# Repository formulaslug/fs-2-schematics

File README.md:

# This is outdated (June 2024)

<p align="center">
  
  <h3 align="center">FS-2 Schematics</h3>

  <p align="center">
    This is the electrical schematics repository for the FS-2 racecar.
    <br />
    <a href="https://github.com/formulaslug/fs-2-schematics/issues">Report Bug</a>
    ·
    <a href="https://github.com/formulaslug/fs-2-schematics/issues">Request Feature</a>
  </p>
</p>

## Getting started
In depth version of how to get started 🏎️
#### Tools that we are using
* [GitHub](https://github.com)
* [KiCAD](https://kicad-pcb.org/)

1) First, download [KiCAD for your specific OS](https://kicad-pcb.org/download/)

2) Next, make sure you have Git installed.

* [GitHub Desktop](https://desktop.github.com/)
If you are *not* tech savvy
* [Git](https://git-scm.com/downloads)
If you are tech savvy 😎

If you installed GitHub desktop, create an account and close the repository.
I recommend cloning the repository into your documents folder.

[How to clone repositories on GitHub desktop](https://docs.github.com/en/free-pro-team@latest/desktop/contributing-and-collaborating-using-github-desktop/cloning-and-forking-repositories-from-github-desktop)

The repository url is: https://github.com/formulaslug/fs-2-schematics

If you are <b>tech savvy</b> and using Git

`$ git clone https://github.com/formulaslug/fs-2-schematics`

3) Setting the project file path correctly on KiCAD

Make sure KiCAD is currently open

Then click on `preferences -> Configure Paths..`

Click on the plus on the bottom right to add a new path variable

On the left, you want it `FS_2_SCHEMATICS` <- all caps

On the right, you want to set the path where you installed the repository (the folder is called `fs-2-schematics`)

Click on the folder on the right, and find `fs-2-schematics` repo like stated above

Should look something like this after its done

Example (might look different if you are using an Mac, or Linux):

Left side | Right side
------------ | -------------
FS_2_SCHEMATICS | Docs\fs-2-schematics

4) Lastly, open up the project

## Contributing guide

## Projects

### BMS

This is the design for the LTC6811-based BMS module, based on the design from fs-1.

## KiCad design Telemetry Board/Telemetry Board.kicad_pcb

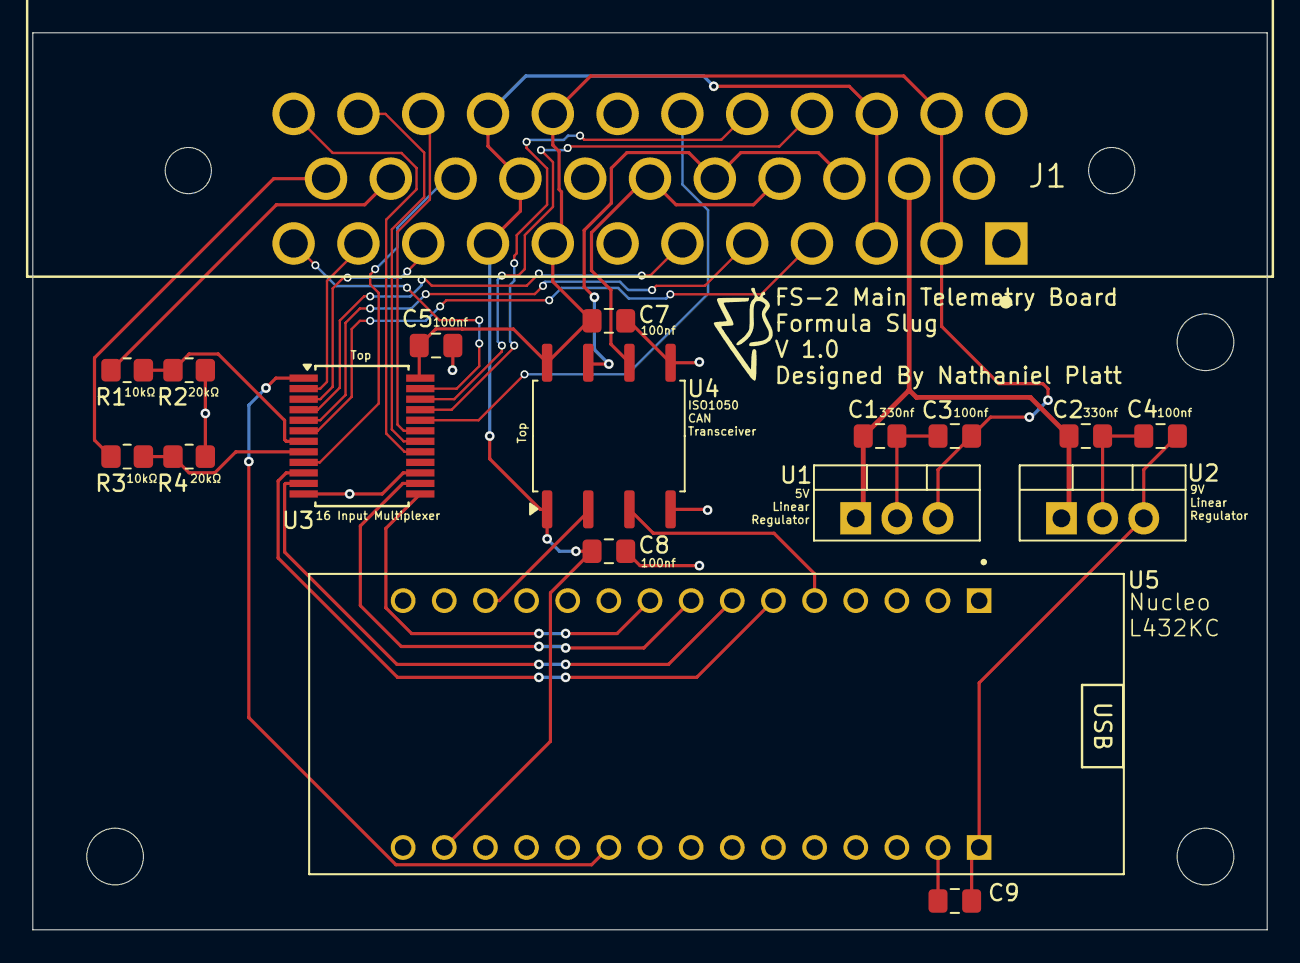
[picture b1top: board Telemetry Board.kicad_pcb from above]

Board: 2 copper layers, 76.2 x 55.4 mm, 18 parts (0 on the bottom side), 31 nets.

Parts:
C1, C2: 330nf; C_0805_2012Metric_Pad1.18x1.45mm_HandSolder
C3, C4, C5, C7, C8, C9: 100nf; C_0805_2012Metric_Pad1.18x1.45mm_HandSolder
J1: 776180-1; TE_776180-1
R1, R3: 10k; R_0805_2012Metric_Pad1.20x1.40mm_HandSolder
R2, R4: 20k; R_0805_2012Metric_Pad1.20x1.40mm_HandSolder
U1: LM7805_TO220; TO-220-3_Vertical
U2: LM7809_TO220; TO-220-3_Vertical
U3: CD74HC4067SM96; SSOP-24_5.3x8.2mm_P0.65mm
U4: ISO1050DUB; SOP-8_6.62x9.15mm_P2.54mm
U5: NUCLEO-L432KC; MODULE_NUCLEO-L432KC

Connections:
+3V3: C8.2, J1.3, J1.9, J1.20, J1.26, J1.32, U4.1 (VCC1), U5.CN4_14 (3V3)
+5V: C3.1, C5.1, C7.2, J1.2, J1.8, J1.25, J1.31, U1.3 (VO), U3.24 (VCC), U4.8 (VCC2)
+9V: C4.1, C9.1, U2.3 (VO), U5.CN4_1 (VIN)
+12V: C1.1, C2.1, J1.14, U1.1 (VI), U2.1 (VI)
/CAN1_RD: U4.2 (RXD), U5.CN3_13 (PA11)
/CAN1_TD: U4.3 (TXD), U5.CN3_5 (PA12)
ADC: U3.1 (COMMON_I_O), U5.CN4_10 (PA3)
Brake Sensor B: J1.23, R3.1
Brake Sensor F: J1.22, R1.1
Brake Sensor F 3V3: R1.2, R2.2, U3.7 (I2)
Brake Sensor R 3V3: R3.2, R4.2, U3.8 (I1)
CAN_H: J1.15, J1.17, U4.7 (CANH)
CAN_L: J1.16, J1.18, U4.6 (CANL)
GND: C1.2, C2.2, C3.2, C4.2, C5.2, C7.1, C8.1, C9.2, J1.1, J1.7, J1.13, J1.19, J1.24, J1.30, R2.1, R4.1, U1.2 (GND), U2.2 (GND), U3.12 (GND), U3.15 (E_N), U4.4 (GND1), U4.5 (GND2), U5.CN4_2 (GND)
S1: U3.10 (S0), U5.CN3_6 (PB0)
S2: U3.11 (S1), U5.CN3_7 (PB7)
S3: U3.14 (S2), U5.CN3_8 (PB6)
S4: U3.13 (S3), U5.CN3_9 (PB1)
Shock Position BL: J1.33, U3.19 (I12)
Shock Position BR: J1.27, U3.22 (I9)
Shock Position FL: J1.10, U3.3 (I6)
Shock Position FR: J1.4, U3.6 (I3)
Steering Sensor: J1.21, U3.9 (I0)
Strain BL: J1.34, U3.18 (I13)
Strain BR: J1.28, U3.21 (I10)
Strain FL: J1.11, U3.2 (I7)
Strain FR: J1.5, U3.5 (I4)
Wheel Speed BL: J1.35, U3.17 (I14)
Wheel Speed BR: J1.29, U3.20 (I11)
Wheel Speed FL: J1.12, U3.23 (I8)
Wheel Speed FR: J1.6, U3.4 (I5)

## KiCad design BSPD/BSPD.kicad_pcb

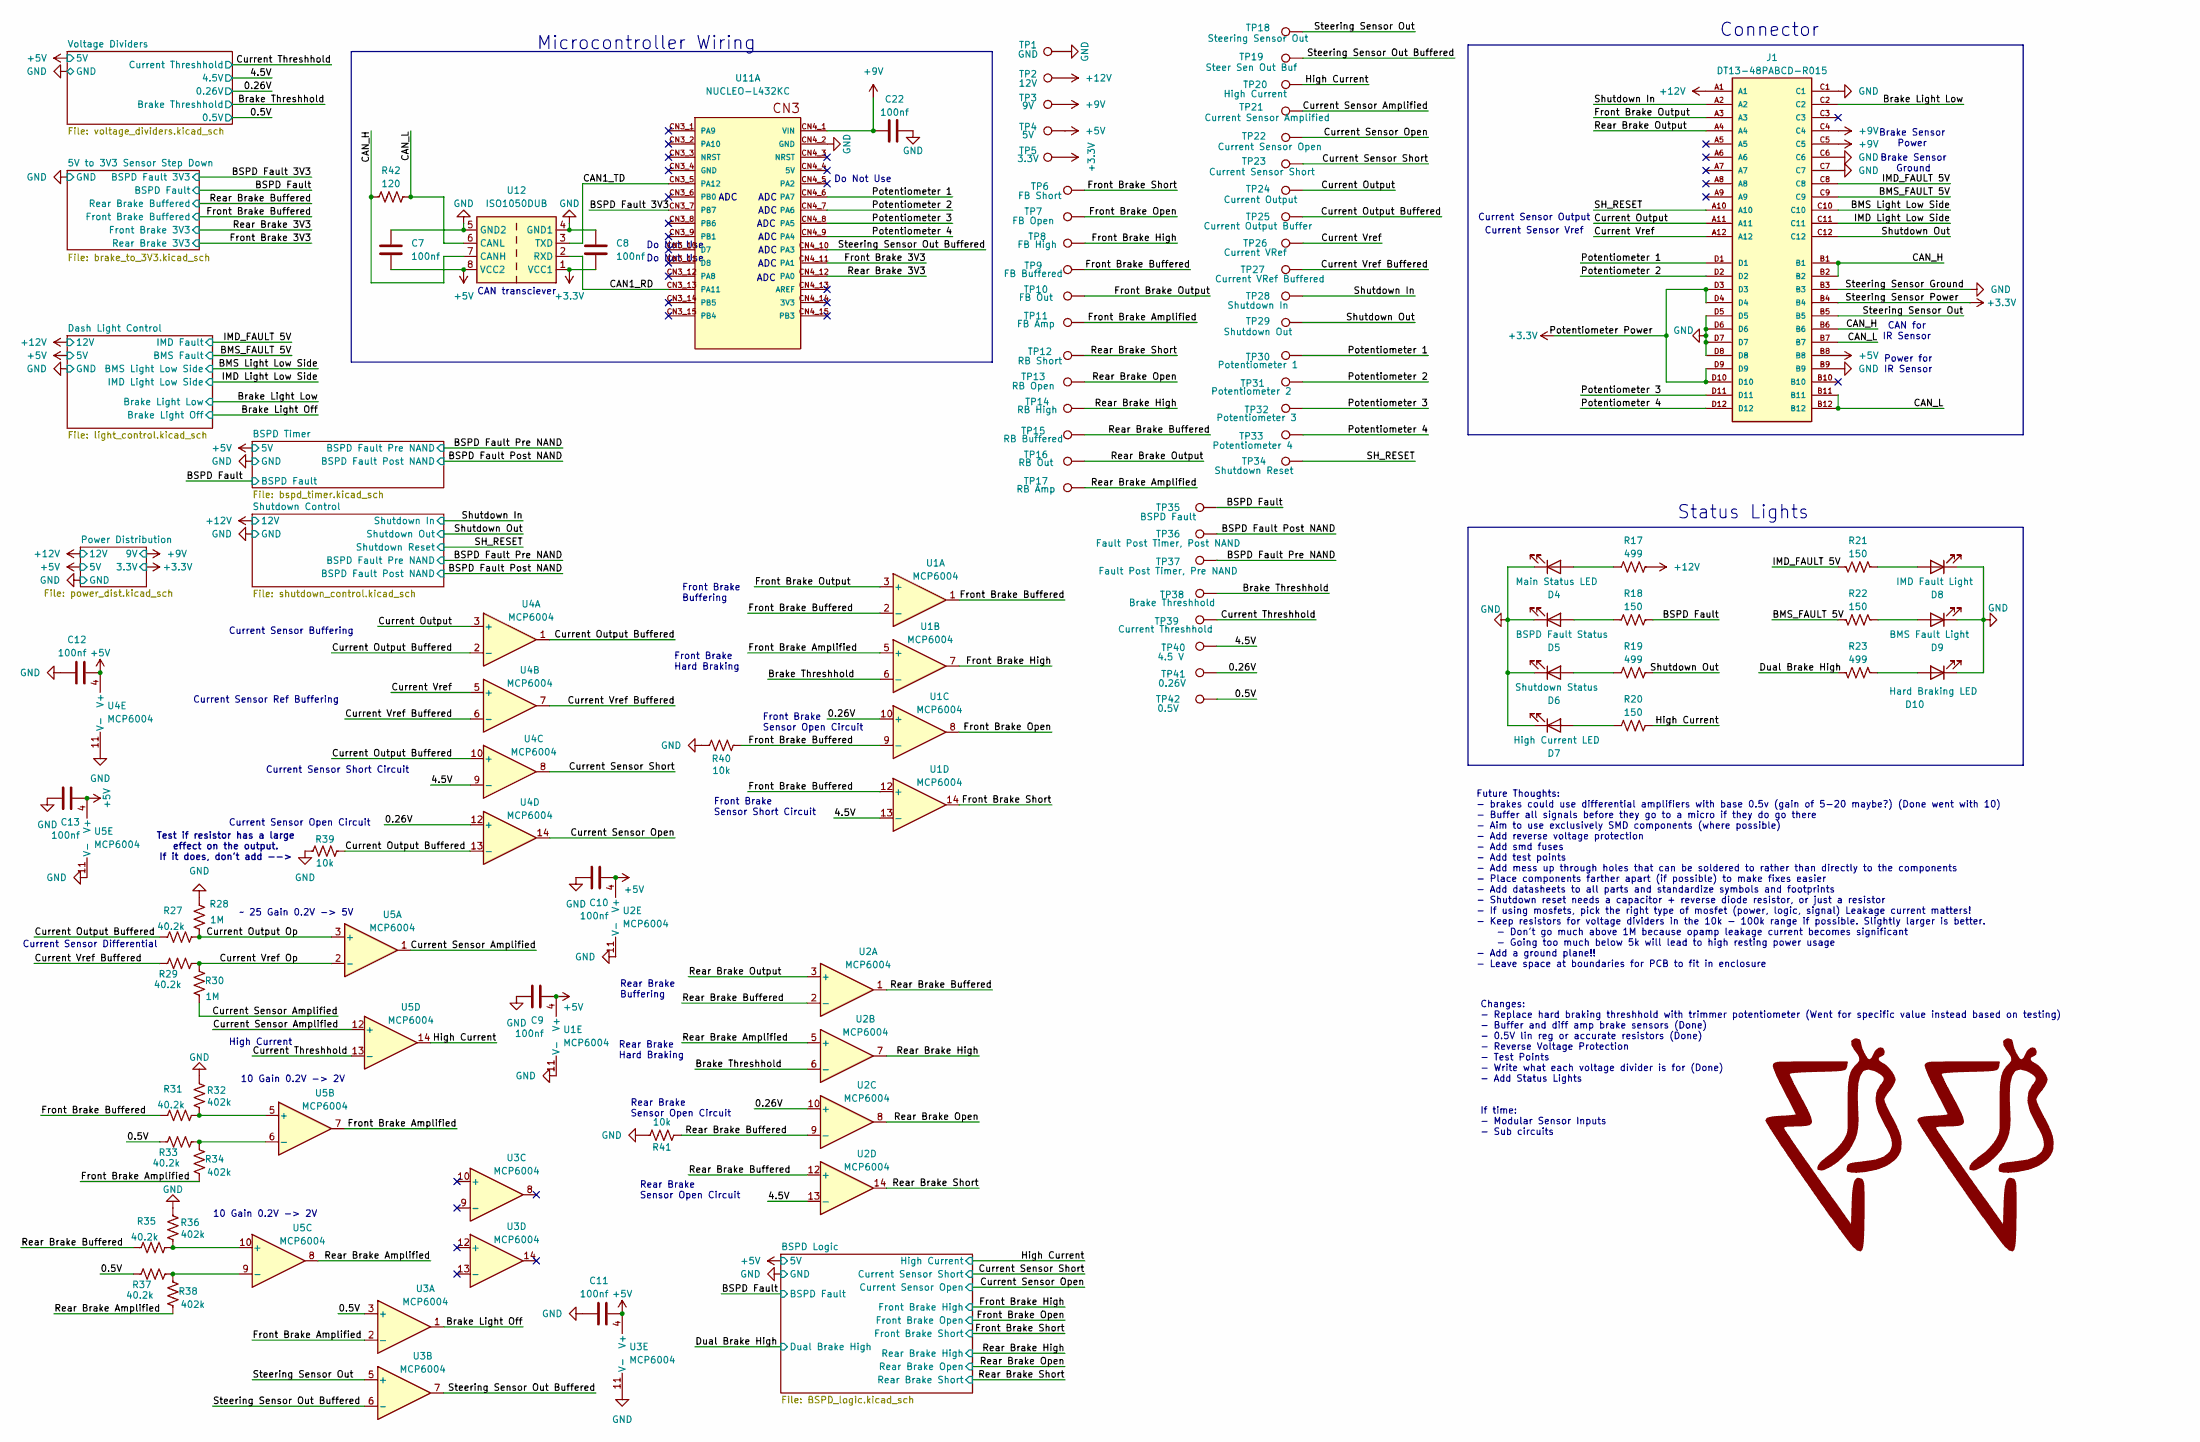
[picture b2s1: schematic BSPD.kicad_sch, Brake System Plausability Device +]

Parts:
C7, C8, C9, C10, C11, C12, C13, C22: 100nf; C_0805_2012Metric_Pad1.18x1.45mm_HandSolder
D4: Main Status LED; D_0805_2012Metric_Pad1.15x1.40mm_HandSolder
D5: BSPD Fault Status; D_0805_2012Metric_Pad1.15x1.40mm_HandSolder
D6: Shutdown Status; D_0805_2012Metric_Pad1.15x1.40mm_HandSolder
D7: High Current LED; D_0805_2012Metric_Pad1.15x1.40mm_HandSolder
D8: IMD Fault Light; D_0805_2012Metric_Pad1.15x1.40mm_HandSolder
D9: BMS Fault Light; D_0805_2012Metric_Pad1.15x1.40mm_HandSolder
D10: Hard Braking LED; D_0805_2012Metric_Pad1.15x1.40mm_HandSolder
G1: FS Logo; FS Logo Big
G2: FS Logo; FORMULA SLUG
J1: DT13-48PABCD-R015; TE_DT13-48PABCD-R015; PARTREV NC
R17, R19, R23: 499; R_0805_2012Metric_Pad1.20x1.40mm_HandSolder
R18, R20, R21, R22: 150; R_0805_2012Metric_Pad1.20x1.40mm_HandSolder
R27, R29, R31, R33, R35, R37: 40.2k; R_0805_2012Metric_Pad1.20x1.40mm_HandSolder
R28, R30: 1M; R_0805_2012Metric_Pad1.20x1.40mm_HandSolder
R32, R34, R36, R38: 402k; R_0805_2012Metric_Pad1.20x1.40mm_HandSolder
R39, R40, R41: 10k; R_0805_2012Metric_Pad1.20x1.40mm_HandSolder
R42: 120; R_0805_2012Metric_Pad1.20x1.40mm_HandSolder
TP1: GND; TestPoint_Loop_D2.50mm_Drill1.0mm
TP2: 12V; TestPoint_Loop_D2.50mm_Drill1.0mm
TP3: 9V; TestPoint_Loop_D2.50mm_Drill1.0mm
TP4: 5V; TestPoint_Loop_D2.50mm_Drill1.0mm
TP5: 3.3V; TestPoint_Loop_D2.50mm_Drill1.0mm
TP6: FB Short; TestPoint_Loop_D2.50mm_Drill1.0mm
TP7: FB Open; TestPoint_Loop_D2.50mm_Drill1.0mm
TP8: FB High; TestPoint_Loop_D2.50mm_Drill1.0mm
TP9: FB Buffered; TestPoint_Loop_D2.50mm_Drill1.0mm
TP10: FB Out; TestPoint_Loop_D2.50mm_Drill1.0mm
TP11: FB Amp; TestPoint_Loop_D2.50mm_Drill1.0mm
TP12: RB Short; TestPoint_Loop_D2.50mm_Drill1.0mm
TP13: RB Open; TestPoint_Loop_D2.50mm_Drill1.0mm
TP14: RB High; TestPoint_Loop_D2.50mm_Drill1.0mm
TP15: RB Buffered; TestPoint_Loop_D2.50mm_Drill1.0mm
TP16: RB Out; TestPoint_Loop_D2.50mm_Drill1.0mm
TP17: RB Amp; TestPoint_Loop_D2.50mm_Drill1.0mm
TP18: Steering Sensor Out; TestPoint_Loop_D2.50mm_Drill1.0mm
TP19: Steer Sen Out Buf; TestPoint_Loop_D2.50mm_Drill1.0mm
TP20: High Current; TestPoint_Loop_D2.50mm_Drill1.0mm
TP21: Current Sensor Amplified; TestPoint_Loop_D2.50mm_Drill1.0mm
TP22: Current Sensor Open; TestPoint_Loop_D2.50mm_Drill1.0mm
TP23: Current Sensor Short; TestPoint_Loop_D2.50mm_Drill1.0mm
TP24: Current Output; TestPoint_Loop_D2.50mm_Drill1.0mm
TP25: Current Output Buffer; TestPoint_Loop_D2.50mm_Drill1.0mm
TP26: Current VRef; TestPoint_Loop_D2.50mm_Drill1.0mm
TP27: Current VRef Buffered; TestPoint_Loop_D2.50mm_Drill1.0mm
TP28: Shutdown In; TestPoint_Loop_D2.50mm_Drill1.0mm
TP29: Shutdown Out; TestPoint_Loop_D2.50mm_Drill1.0mm
TP30: Potentiometer 1; TestPoint_Loop_D2.50mm_Drill1.0mm
TP31: Potentiometer 2; TestPoint_Loop_D2.50mm_Drill1.0mm
TP32: Potentiometer 3; TestPoint_Loop_D2.50mm_Drill1.0mm
TP33: Potentiometer 4; TestPoint_Loop_D2.50mm_Drill1.0mm
TP34: Shutdown Reset; TestPoint_Loop_D2.50mm_Drill1.0mm
TP35: BSPD Fault; TestPoint_Loop_D2.50mm_Drill1.0mm
TP36: Fault Post Timer, Post NAND; TestPoint_Loop_D2.50mm_Drill1.0mm
TP37: Fault Post Timer, Pre NAND; TestPoint_Loop_D2.50mm_Drill1.0mm
TP38: Brake Threshhold; TestPoint_Loop_D2.50mm_Drill1.0mm
TP39: Current Threshhold; TestPoint_Loop_D2.50mm_Drill1.0mm
TP40: 4.5 V; TestPoint_Loop_D2.50mm_Drill1.0mm
TP41: 0.26V; TestPoint_Loop_D2.50mm_Drill1.0mm
TP42: 0.5V; TestPoint_Loop_D2.50mm_Drill1.0mm
U1, U2, U3, U4, U5: MCP6004; SOIC-14_3.9x8.7mm_P1.27mm
U11: NUCLEO-L432KC; MODULE_NUCLEO-L432KC; PARTREV N/A
U12: ISO1050DUB; SOP-8_6.62x9.15mm_P2.54mm

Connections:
+3.3V: C8.2, J1.B4, J1.D3, J1.D4, J1.D9, J1.D10, TP5.1, U12.1 (VCC1); also elsewhere on the board
+5V: C7.2, C9.2, C10.2, C11.2, C12.2, C13.2, J1.B8, TP4.1, U1.4 (V+), U2.4 (V+), U3.4 (V+), U4.4 (V+), U5.4 (V+), U12.8 (VCC2); also elsewhere on the board
+9V: C22.1, J1.C4, J1.C5, TP3.1, U11.CN4_1 (VIN); also elsewhere on the board
+12V: J1.A1, R17.1, TP2.1; also elsewhere on the board
/0.5V: R33.1, R37.1, TP42.1, U3.3 (+); also elsewhere on the board
/0.26V: TP41.1, U1.10 (+), U2.10 (+), U4.12 (+); also elsewhere on the board
/4.5V: TP40.1, U1.13 (-), U2.13 (-), U4.9 (-); also elsewhere on the board
/BMS Light Low Side: J1.C10; also elsewhere on the board
/BMS_FAULT 5V: J1.C9, R22.1; also elsewhere on the board
/BSPD Fault: R18.1, TP35.1; also elsewhere on the board
/BSPD Fault 3V3: U11.CN3_7 (PB7); also elsewhere on the board
/BSPD Fault Post NAND: TP36.1; also elsewhere on the board
/BSPD Fault Pre NAND: TP37.1; also elsewhere on the board
/Brake Light Low: J1.C2; also elsewhere on the board
/Brake Light Off: U3.1; also elsewhere on the board
/Brake Threshhold: TP38.1, U1.6 (-), U2.6 (-); also elsewhere on the board
/CAN1_RD: U11.CN3_13 (PA11), U12.2 (RXD)
/CAN1_TD: U11.CN3_5 (PA12), U12.3 (TXD)
/CAN_H: J1.B1, J1.B2, J1.B6, R42.2, U12.7 (CANH)
/CAN_L: J1.B7, J1.B11, J1.B12, R42.1, U12.6 (CANL)
/Current Output: J1.A11, TP24.1, U4.3 (+)
/Current Output Buffered: R27.2, R39.2, TP25.1, U4.1, U4.2 (-), U4.10 (+), U4.13 (-)
/Current Output Op: R27.1, R28.1, U5.3 (+)
/Current Sensor Amplified: R30.1, TP21.1, U5.1, U5.12 (+)
/Current Sensor Open: TP22.1, U4.14; also elsewhere on the board
/Current Sensor Short: TP23.1, U4.8; also elsewhere on the board
/Current Threshhold: TP39.1, U5.13 (-); also elsewhere on the board
/Current Vref: J1.A12, TP26.1, U4.5 (+)
/Current Vref Buffered: R29.1, TP27.1, U4.6 (-), U4.7
/Current Vref Op: R29.2, R30.2, U5.2 (-)
/Dual Brake High: R23.1; also elsewhere on the board
/Front Brake 3V3: U11.CN4_11 (PA1); also elsewhere on the board
/Front Brake Amplified: R34.1, TP11.1, U1.5 (+), U3.2 (-), U5.7
/Front Brake Buffered: R31.2, R40.1, TP9.1, U1.1, U1.2 (-), U1.9 (-), U1.12 (+); also elsewhere on the board
/Front Brake High: TP8.1, U1.7; also elsewhere on the board
/Front Brake Open: TP7.1, U1.8; also elsewhere on the board
/Front Brake Output: J1.A3, TP10.1, U1.3 (+)
/Front Brake Short: TP6.1, U1.14; also elsewhere on the board
/High Current: R20.1, TP20.1, U5.14; also elsewhere on the board
/IMD Light Low Side: J1.C11; also elsewhere on the board
/IMD_FAULT 5V: J1.C8, R21.1; also elsewhere on the board
/Potentiometer 1: J1.D1, TP30.1, U11.CN4_6 (PA7)
/Potentiometer 2: J1.D2, TP31.1, U11.CN4_7 (PA6)
/Potentiometer 3: J1.D11, TP32.1, U11.CN4_8 (PA5)
/Potentiometer 4: J1.D12, TP33.1, U11.CN4_9 (PA4)
/Rear Brake 3V3: U11.CN4_12 (PA0); also elsewhere on the board
/Rear Brake Amplified: R38.1, TP17.1, U2.5 (+), U5.8
/Rear Brake Buffered: R35.2, R41.2, TP15.1, U2.1, U2.2 (-), U2.9 (-), U2.12 (+); also elsewhere on the board
/Rear Brake High: TP14.1, U2.7; also elsewhere on the board
/Rear Brake Open: TP13.1, U2.8; also elsewhere on the board
/Rear Brake Output: J1.A4, TP16.1, U2.3 (+)
/Rear Brake Short: TP12.1, U2.14; also elsewhere on the board
/SH_RESET: J1.A10, TP34.1; also elsewhere on the board
/Shutdown In: J1.A2, TP28.1; also elsewhere on the board
/Shutdown Out: J1.C12, R19.1, TP29.1; also elsewhere on the board
/Steering Sensor Out: J1.B5, TP18.1, U3.5 (+)
/Steering Sensor Out Buffered: TP19.1, U3.6 (-), U3.7, U11.CN4_10 (PA3)
GND: C7.1, C8.1, C9.1, C10.1, C11.1, C12.1, C13.1, C22.2, D4.1 (K), D5.1 (K), D6.1 (K), D7.1 (K), D8.1 (K), D9.1 (K), D10.1 (K), J1.B3, J1.B9, J1.C1, J1.C6, J1.C7, J1.D5, J1.D6, J1.D7, J1.D8, R28.2, R32.2, R36.2, R39.1, R40.2, R41.1, TP1.1, U1.11 (V-), U2.11 (V-), U3.11 (V-), U4.11 (V-), U5.11 (V-), U11.CN4_2 (GND), U12.4 (GND1), U12.5 (GND2); also elsewhere on the board
unnamed: D4.2 (A), R17.2
unnamed: D5.2 (A), R18.2
unnamed: D6.2 (A), R19.2
unnamed: D7.2 (A), R20.2
unnamed: D8.2 (A), R21.2
unnamed: D9.2 (A), R22.2
unnamed: D10.2 (A), R23.2
unnamed: R31.1, R32.1, U5.5 (+)
unnamed: R33.2, R34.2, U5.6 (-)
unnamed: R35.1, R36.1, U5.10 (+)
unnamed: R37.2, R38.2, U5.9 (-)

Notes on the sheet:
Future Thoughts: - brakes could use differential amplifiers with base 0.5v (gain of 5-20 maybe?) (Done went with 10) - Buffer all signals before they go to a micro if they do go there - Aim to use exclusively SMD components (where possible) - Add reverse voltage protection - Add smd fuses - Add tes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
CAN for IR Sensor
ADC
Do Not Use
Rear Brake Buffering
Power for IR Sensor
Current Sensor Output
Microcontroller Wiring
Brake Sensor Power
High Current
Rear Brake Sensor Open Circuit
Current Sensor Buffering
10 Gain 0.2V -> 2V
Rear Brake Hard Braking
Front Brake Buffering
CAN transciever
Current Sensor Open Circuit
Front Brake Sensor Open Circuit
Current Sensor Vref
Changes: - Replace hard braking threshhold with trimmer potentiometer (Went for specific value instead based on testing) - Buffer and diff amp brake sensors (Done) - 0.5V lin reg or accurate resistors (Done) - Reverse Voltage Protection - Test Points - Write what each voltage divider is for (Done) 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
Current Sensor Differential
Connector
Test if resistor has a large effect on the output. If it does, don't add -->
Current Sensor Short Circuit
Status Lights
Front Brake Sensor Short Circuit
Current Sensor Ref Buffering
~ 25 Gain 0.2V -> 5V
Brake Sensor Ground
Front Brake Hard Braking

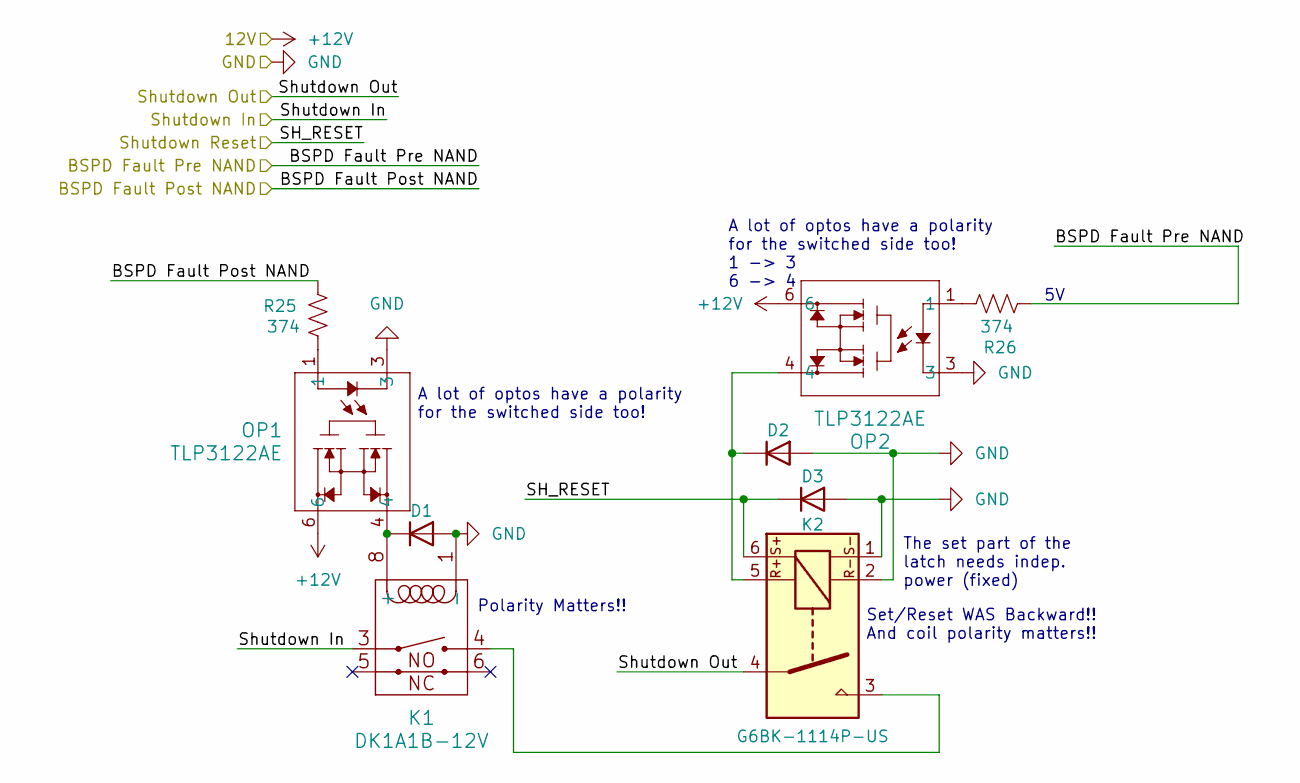
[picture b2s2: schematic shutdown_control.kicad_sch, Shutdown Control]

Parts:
D1, D2, D3: D; D_2010_5025Metric_Pad1.52x2.65mm_HandSolder
K1: DK1A1B-12V; RELAY_DK2A_PAN
K2: G6BK-1114P-US; Omron G6BK-1114P-US
OP1, OP2: TLP3122AE; OptoCoupler 6-SOP
R25, R26: 374; R_0805_2012Metric_Pad1.20x1.40mm_HandSolder

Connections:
+12V: OP1.6, OP2.6; also elsewhere on the board
/BSPD Fault Post NAND: R25.2; also elsewhere on the board
/BSPD Fault Pre NAND: R26.1; also elsewhere on the board
/SH_RESET: D3.1 (K), K2.6; also elsewhere on the board
/Shutdown In: K1.3; also elsewhere on the board
/Shutdown Out: K2.4; also elsewhere on the board
GND: D1.2 (A), D2.2 (A), D3.2 (A), K1.1 (-), K2.1, K2.2, OP1.3, OP2.3; also elsewhere on the board
unnamed: D1.1 (K), K1.8 (+), OP1.4
unnamed: D2.1 (K), K2.5, OP2.4
unnamed: K1.4, K2.3
unnamed: OP1.1, R25.1
unnamed: OP2.1, R26.2

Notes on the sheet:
A lot of optos have a polarity for the switched side too!
Set/Reset WAS Backward!! And coil polarity matters!!
A lot of optos have a polarity for the switched side too! 1 -> 3 6 -> 4
The set part of the latch needs indep. power (fixed)
Polarity Matters!!

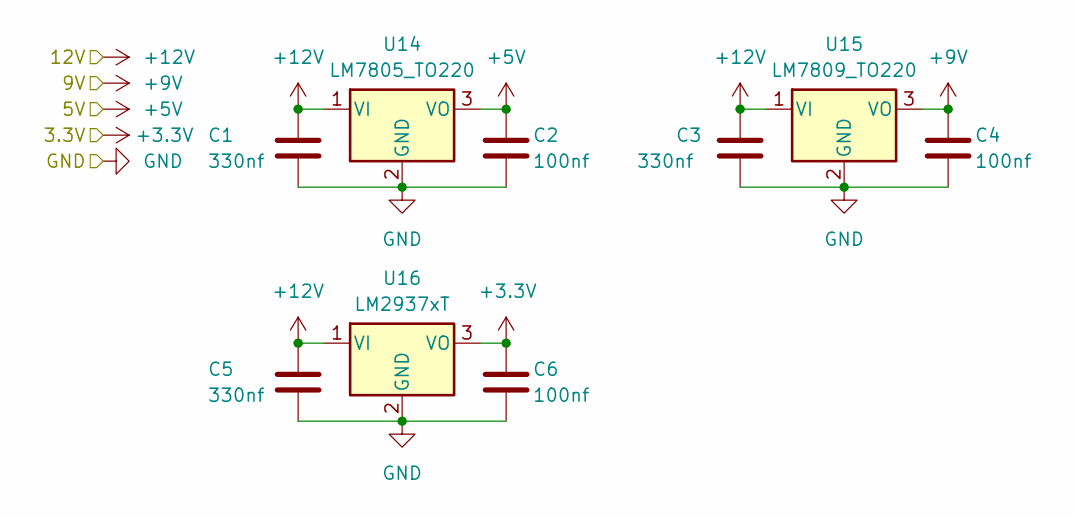
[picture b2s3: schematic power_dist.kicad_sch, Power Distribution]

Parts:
C1, C3, C5: 330nf; C_0805_2012Metric_Pad1.18x1.45mm_HandSolder
C2, C4, C6: 100nf; C_0805_2012Metric_Pad1.18x1.45mm_HandSolder
U14: LM7805_TO220; TO-220-3_Vertical
U15: LM7809_TO220; TO-220-3_Vertical
U16: LM2937xT; TO-220-3_Vertical

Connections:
+3.3V: C6.1, U16.3 (VO); also elsewhere on the board
+5V: C2.1, U14.3 (VO); also elsewhere on the board
+9V: C4.1, U15.3 (VO); also elsewhere on the board
+12V: C1.1, C3.1, C5.1, U14.1 (VI), U15.1 (VI), U16.1 (VI); also elsewhere on the board
GND: C1.2, C2.2, C3.2, C4.2, C5.2, C6.2, U14.2 (GND), U15.2 (GND), U16.2 (GND); also elsewhere on the board

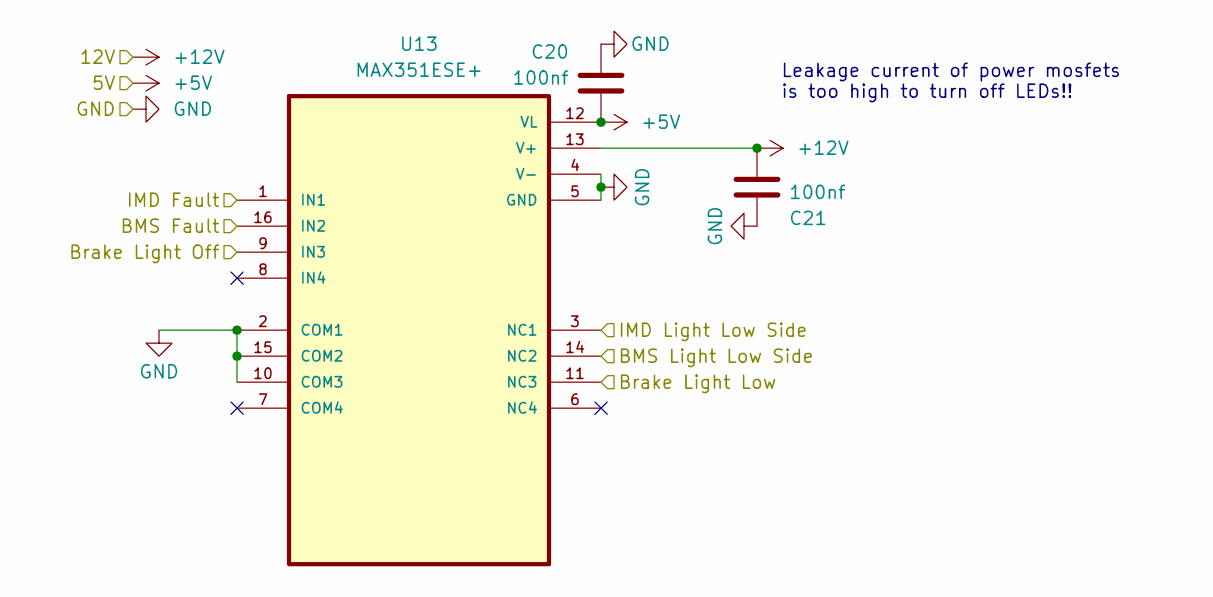
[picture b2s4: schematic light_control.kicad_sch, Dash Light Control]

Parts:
C20, C21: 100nf; C_0805_2012Metric_Pad1.18x1.45mm_HandSolder
U13: MAX351ESE+; SOIC127P600X175-16N

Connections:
+5V: C20.1, U13.12 (VL); also elsewhere on the board
+12V: C21.1, U13.13 (V+); also elsewhere on the board
/BMS Light Low Side: U13.14 (NC2); also elsewhere on the board
/BMS_FAULT 5V: U13.16 (IN2); also elsewhere on the board
/Brake Light Low: U13.11 (NC3); also elsewhere on the board
/Brake Light Off: U13.9 (IN3); also elsewhere on the board
/IMD Light Low Side: U13.3 (NC1); also elsewhere on the board
/IMD_FAULT 5V: U13.1 (IN1); also elsewhere on the board
GND: C20.2, C21.2, U13.2 (COM1), U13.4 (V-), U13.5 (GND), U13.10 (COM3), U13.15 (COM2); also elsewhere on the board

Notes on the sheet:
Leakage current of power mosfets is too high to turn off LEDs!!

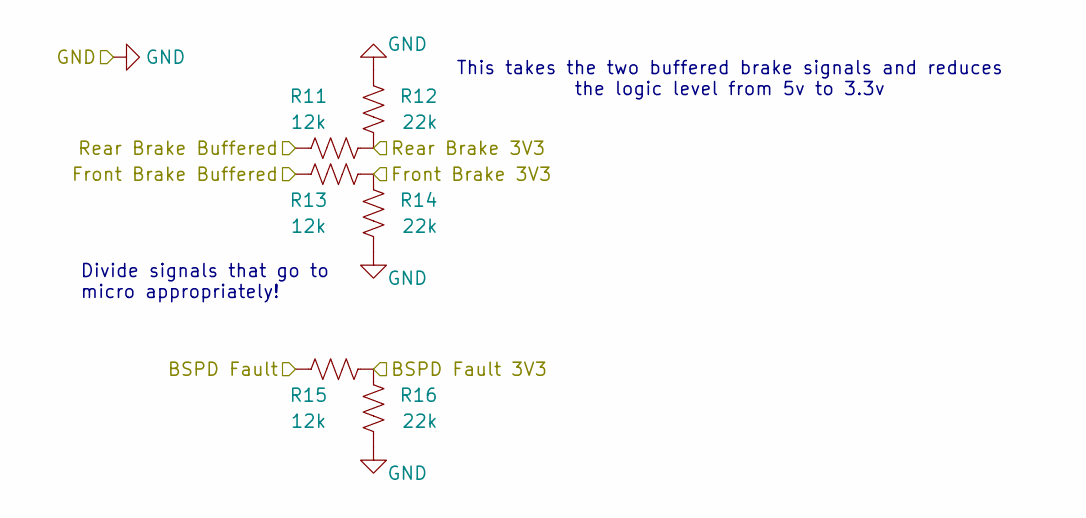
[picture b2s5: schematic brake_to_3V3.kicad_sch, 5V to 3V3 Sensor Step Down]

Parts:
R11, R13, R15: 12k; R_0805_2012Metric_Pad1.20x1.40mm_HandSolder
R12, R14, R16: 22k; R_0805_2012Metric_Pad1.20x1.40mm_HandSolder

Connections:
/BSPD Fault: R15.1; also elsewhere on the board
/BSPD Fault 3V3: R15.2, R16.2; also elsewhere on the board
/Front Brake 3V3: R11.2, R12.1; also elsewhere on the board
/Front Brake Buffered: R13.1; also elsewhere on the board
/Rear Brake 3V3: R13.2, R14.2; also elsewhere on the board
/Rear Brake Buffered: R11.1; also elsewhere on the board
GND: R12.2, R14.1, R16.1; also elsewhere on the board

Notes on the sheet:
Divide signals that go to micro appropriately!
This takes the two buffered brake signals and reduces the logic level from 5v to 3.3v

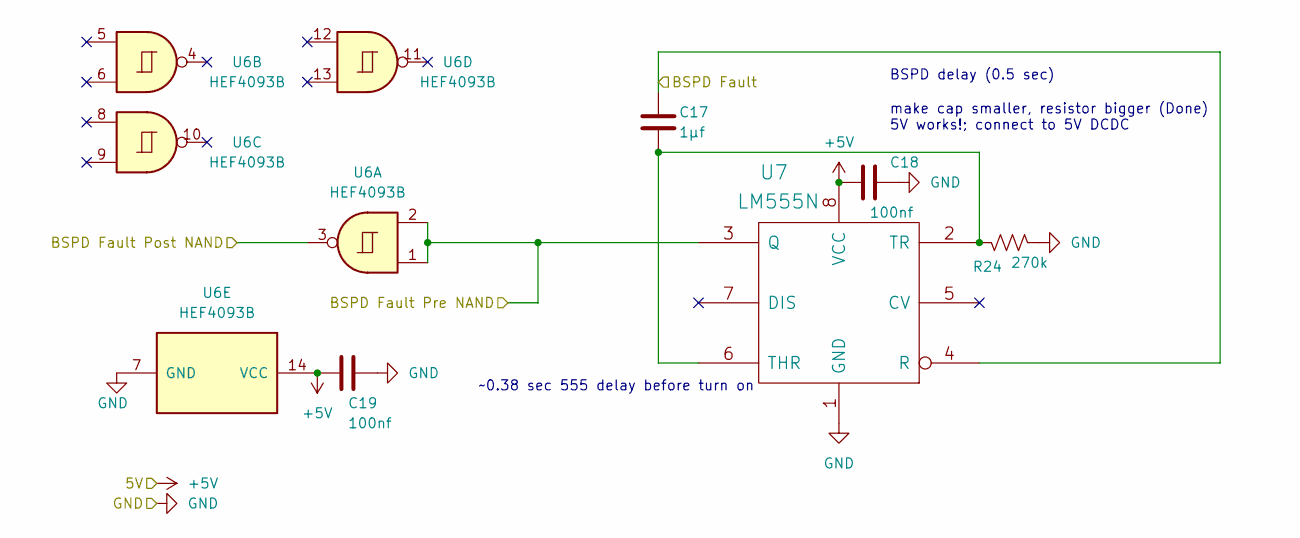
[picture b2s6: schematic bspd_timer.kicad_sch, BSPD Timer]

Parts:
C17: 1μf; C_0805_2012Metric_Pad1.18x1.45mm_HandSolder
C18, C19: 100nf; C_0805_2012Metric_Pad1.18x1.45mm_HandSolder
R24: 270k; R_0805_2012Metric_Pad1.20x1.40mm_HandSolder
U6: HEF4093B; SOIC-14_3.9x8.7mm_P1.27mm
U7: LM555N; DIP-8_W7.62mm

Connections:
+5V: C18.2, C19.2, U6.14 (VCC), U7.8 (VCC); also elsewhere on the board
/BSPD Fault: C17.1, U7.4 (R); also elsewhere on the board
/BSPD Fault Post NAND: U6.3; also elsewhere on the board
/BSPD Fault Pre NAND: U6.1, U6.2, U7.3 (Q); also elsewhere on the board
GND: C18.1, C19.1, R24.2, U6.7 (GND), U7.1 (GND); also elsewhere on the board
unnamed: C17.2, R24.1, U7.2 (TR), U7.6 (THR)

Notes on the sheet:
~0.38 sec 555 delay before turn on
BSPD delay (0.5 sec)
make cap smaller, resistor bigger (Done) 5V works!; connect to 5V DCDC

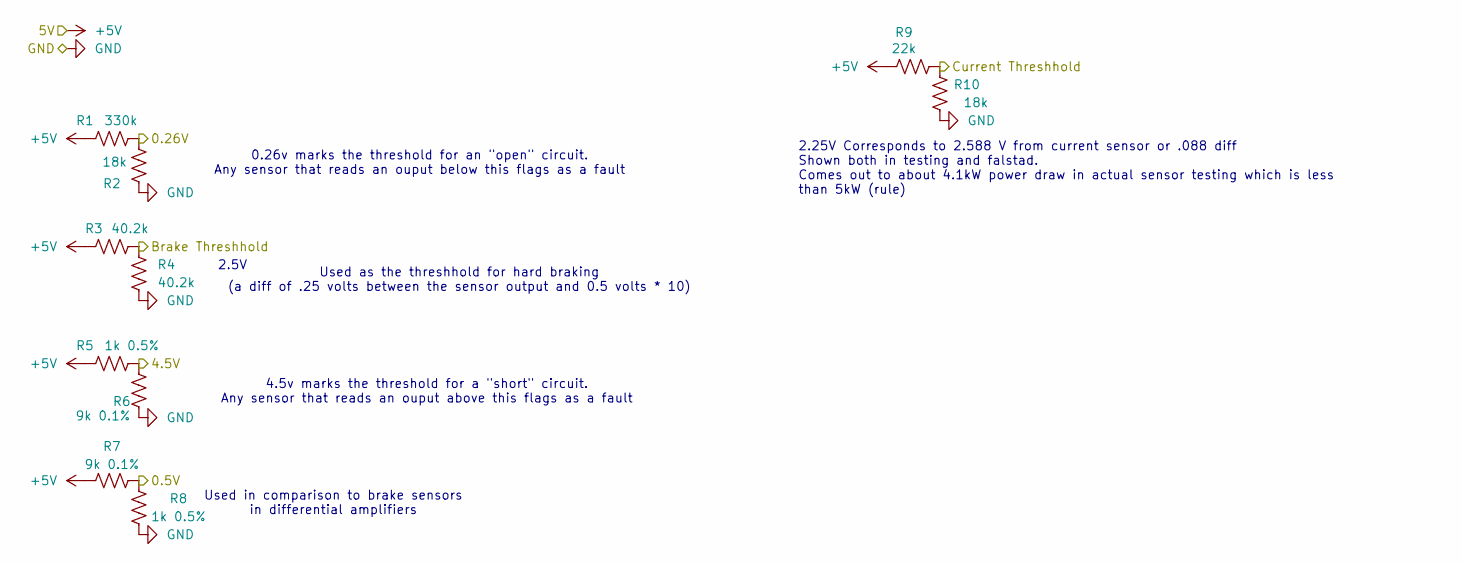
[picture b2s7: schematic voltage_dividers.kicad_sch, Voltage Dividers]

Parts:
R1: 330k; R_0805_2012Metric_Pad1.20x1.40mm_HandSolder
R2, R10: 18k; R_0805_2012Metric_Pad1.20x1.40mm_HandSolder
R3, R4: 40.2k; R_0805_2012Metric_Pad1.20x1.40mm_HandSolder
R5, R8: 1k 0.5%; R_0805_2012Metric_Pad1.20x1.40mm_HandSolder
R6, R7: 9k 0.1%; R_0805_2012Metric_Pad1.20x1.40mm_HandSolder
R9: 22k; R_0805_2012Metric_Pad1.20x1.40mm_HandSolder

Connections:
+5V: R1.1, R3.1, R5.1, R7.1, R9.2; also elsewhere on the board
/0.5V: R7.2, R8.2; also elsewhere on the board
/0.26V: R1.2, R2.1; also elsewhere on the board
/4.5V: R5.2, R6.1; also elsewhere on the board
/Brake Threshhold: R3.2, R4.1; also elsewhere on the board
/Current Threshhold: R9.1, R10.1; also elsewhere on the board
GND: R2.2, R4.2, R6.2, R8.1, R10.2; also elsewhere on the board

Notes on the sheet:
Used in comparison to brake sensors in differential amplifiers
2.25V Corresponds to 2.588 V from current sensor or .088 diff Shown both in testing and falstad. Comes out to about 4.1kW power draw in actual sensor testing which is less than 5kW (rule)
0.26v marks the threshold for an "open" circuit. Any sensor that reads an ouput below this flags as a fault
2.5V
Used as the threshhold for hard braking (a diff of .25 volts between the sensor output and 0.5 volts * 10)
4.5v marks the threshold for a "short" circuit. Any sensor that reads an ouput above this flags as a fault

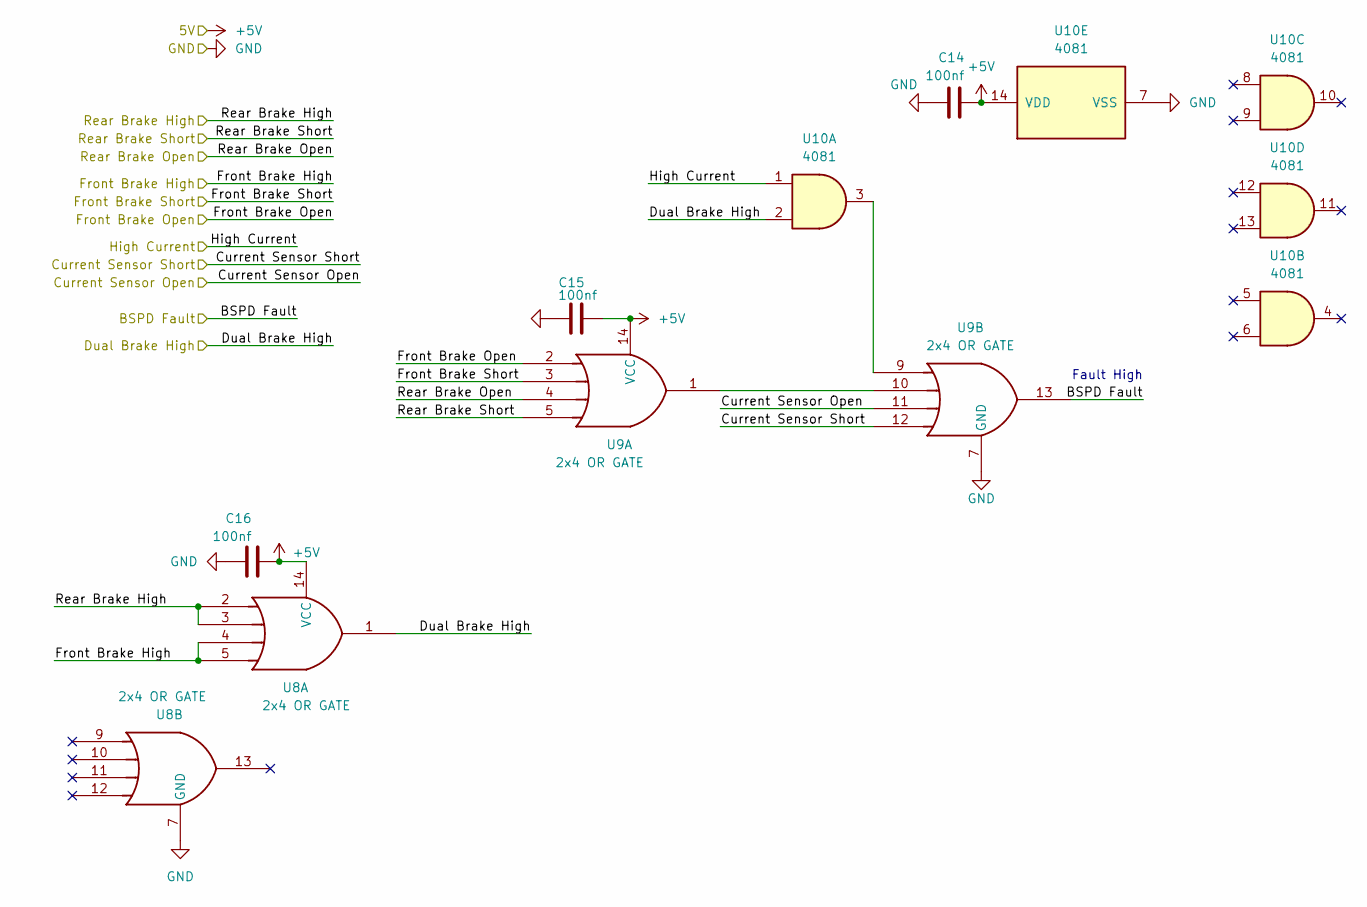
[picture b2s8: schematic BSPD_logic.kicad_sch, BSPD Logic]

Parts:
C14, C15, C16: 100nf; C_0805_2012Metric_Pad1.18x1.45mm_HandSolder
U8, U9: 2x4 OR GATE; DIP-14_W7.62mm
U10: 4081; SOIC-14_3.9x8.7mm_P1.27mm

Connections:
+5V: C14.2, C15.2, C16.2, U8.14 (VCC), U9.14 (VCC), U10.14 (VDD); also elsewhere on the board
/BSPD Fault: U9.13; also elsewhere on the board
/Current Sensor Open: U9.11; also elsewhere on the board
/Current Sensor Short: U9.12; also elsewhere on the board
/Dual Brake High: U8.1, U10.2; also elsewhere on the board
/Front Brake High: U8.4, U8.5; also elsewhere on the board
/Front Brake Open: U9.2; also elsewhere on the board
/Front Brake Short: U9.3; also elsewhere on the board
/High Current: U10.1; also elsewhere on the board
/Rear Brake High: U8.2, U8.3; also elsewhere on the board
/Rear Brake Open: U9.4; also elsewhere on the board
/Rear Brake Short: U9.5; also elsewhere on the board
GND: C14.1, C15.1, C16.1, U8.7 (GND), U9.7 (GND), U10.7 (VSS); also elsewhere on the board
unnamed: U9.1, U9.10
unnamed: U9.9, U10.3

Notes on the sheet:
Fault High

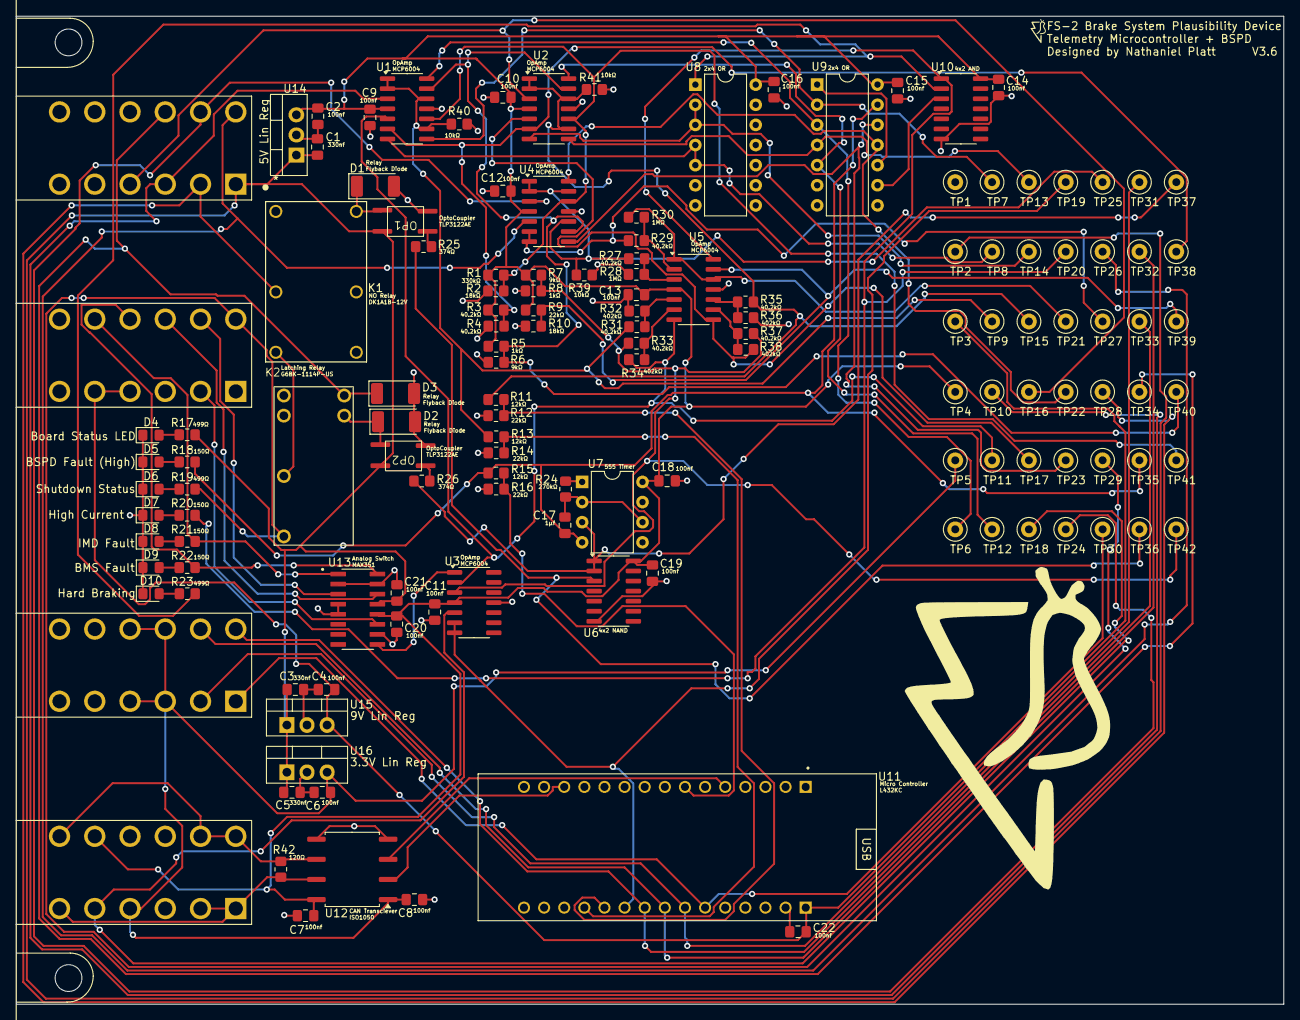
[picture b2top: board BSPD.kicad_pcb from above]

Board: 2 copper layers, 160.0 x 124.7 mm, 139 parts (0 on the bottom side), 77 nets.
